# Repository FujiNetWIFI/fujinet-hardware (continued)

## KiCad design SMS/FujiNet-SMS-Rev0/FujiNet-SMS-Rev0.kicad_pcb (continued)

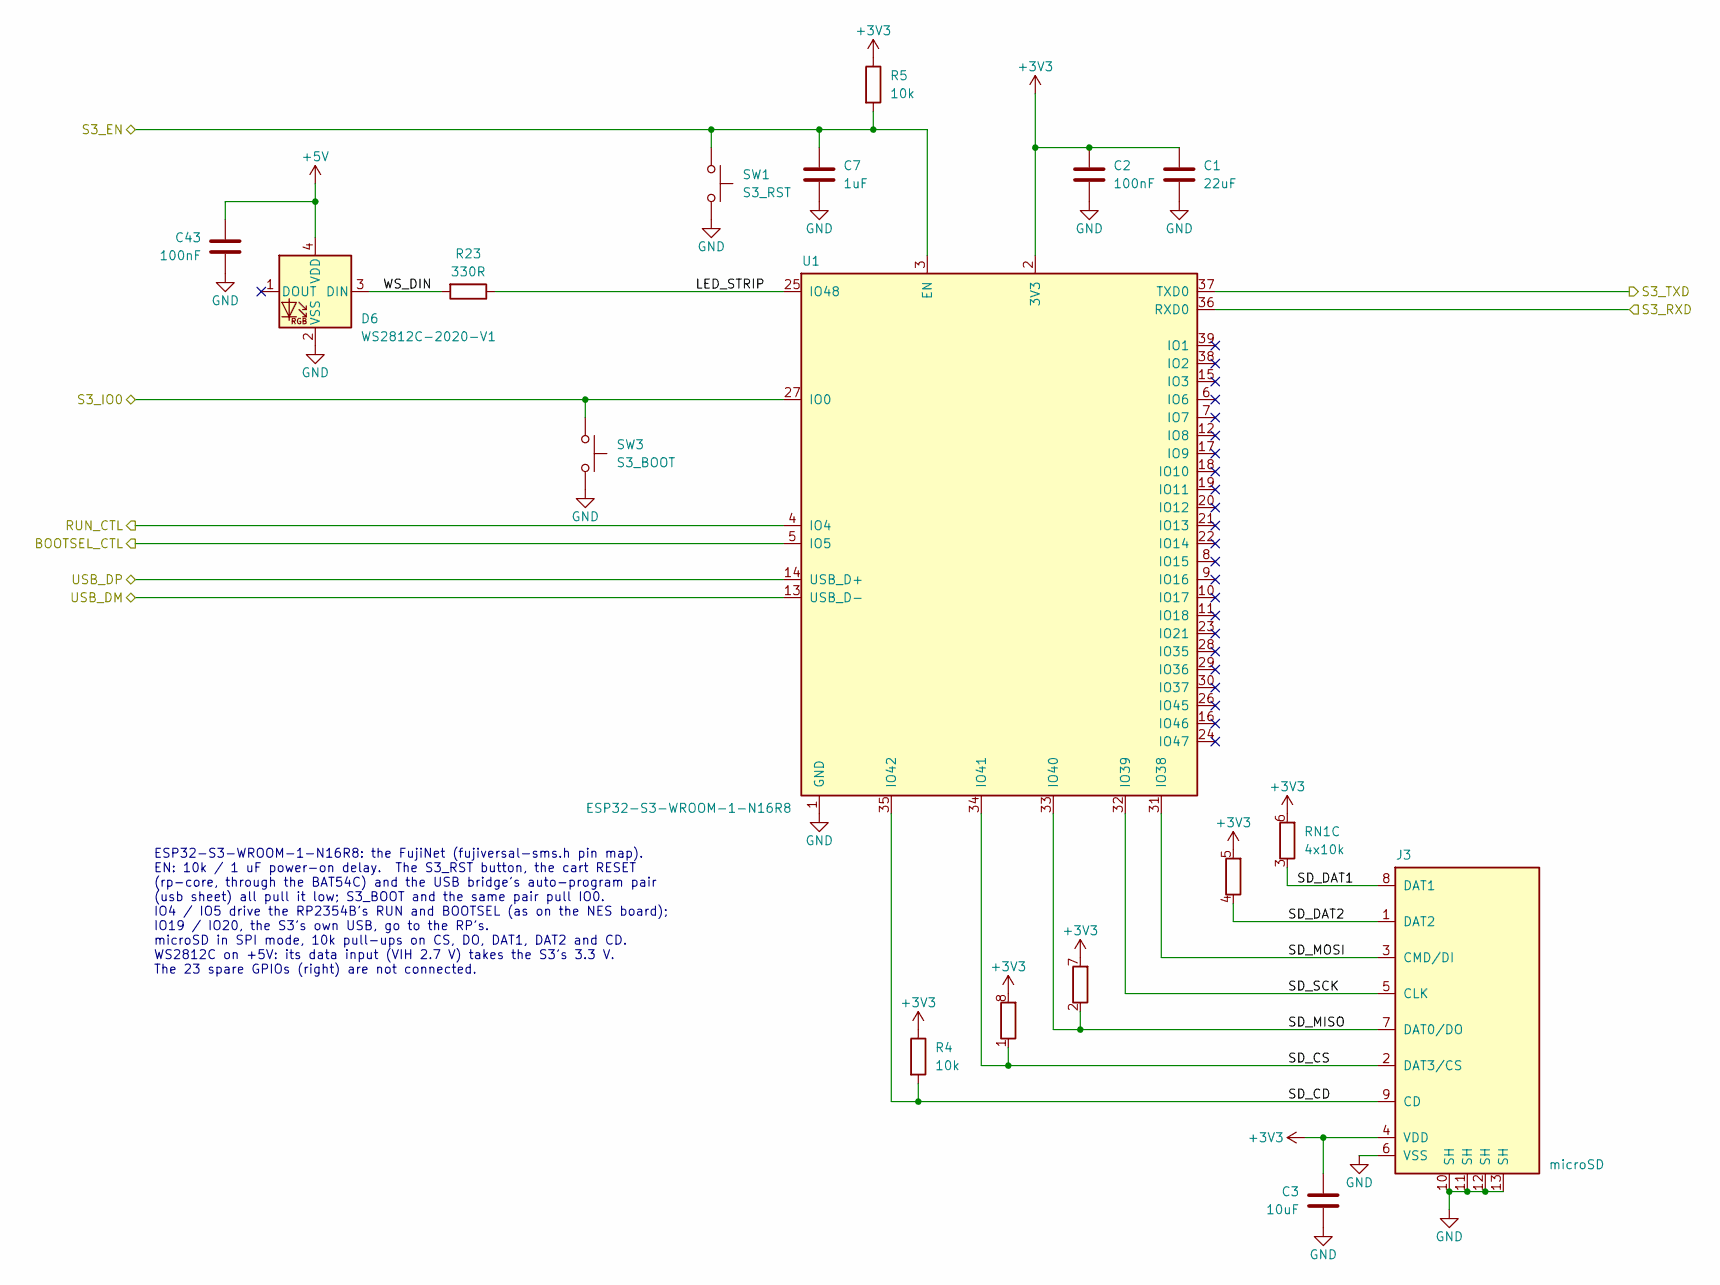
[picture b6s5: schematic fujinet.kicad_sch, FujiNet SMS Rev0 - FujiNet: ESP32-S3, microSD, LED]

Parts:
C1: 22uF; C_0805_2012Metric; MPN CL21A226MAQNNNE; LCSC C45783
C2, C43: 100nF; C_0603_1608Metric; MPN CC0603KRX7R9BB104; LCSC C14663
C3: 10uF; C_0603_1608Metric; MPN CL10A106KP8NNNC; LCSC C19702
C7: 1uF; C_0603_1608Metric; MPN CL10A105KB8NNNC; LCSC C15849
D6: WS2812C-2020-V1; LED_WS2812B-2020_PLCC4_2.0x2.0mm; MPN WS2812C-2020-V1; LCSC C2976072
J3: microSD; TF-SMD_TF-015; MPN TF-015; LCSC C113206
R4, R5: 10k; R_0603_1608Metric; MPN 0603WAF1002T5E; LCSC C25804
R23: 330R; R_0603_1608Metric; MPN 0603WAF3300T5E; LCSC C23138
RN1: 4x10k; R_Array_Convex_4x0603; MPN 4D03WGJ0103T5E; LCSC C29718
SW1: S3_RST; SW_SPST_TS-1187A; MPN TS-1187A-B-A-B; LCSC C318884
SW3: S3_BOOT; SW_SPST_TS-1187A; MPN TS-1187A-B-A-B; LCSC C318884
U1: ESP32-S3-WROOM-1-N16R8; ESP32-S3-WROOM-1; MPN ESP32-S3-WROOM-1-N16R8; LCSC C2913202

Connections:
+3V3: C1.1, C2.1, C3.1, J3.4 (VDD), R4.1, R5.1, RN1.5 (R4.2), RN1.6 (R3.2), RN1.7 (R2.2), RN1.8 (R1.2), U1.2 (3V3); also elsewhere on the board
+5V: C43.1, D6.4 (VDD); also elsewhere on the board
/BOOTSEL_CTL: U1.5 (IO5); also elsewhere on the board
/RUN_CTL: U1.4 (IO4); also elsewhere on the board
/S3_EN: C7.1, R5.2, SW1.1, U1.3 (EN); also elsewhere on the board
/S3_IO0: SW3.1, U1.27 (IO0); also elsewhere on the board
/S3_RXD: U1.36 (RXD0); also elsewhere on the board
/S3_TXD: U1.37 (TXD0); also elsewhere on the board
/USB_DM: U1.13 (USB_D-); also elsewhere on the board
/USB_DP: U1.14 (USB_D+); also elsewhere on the board
/fujinet/LED_STRIP: R23.1, U1.25 (IO48)
/fujinet/SD_CD: J3.9 (CD), R4.2, U1.35 (IO42)
/fujinet/SD_CS: J3.2 (DAT3/CS), RN1.1 (R1.1), U1.34 (IO41)
/fujinet/SD_DAT1: J3.8 (DAT1), RN1.3 (R3.1)
/fujinet/SD_DAT2: J3.1 (DAT2), RN1.4 (R4.1)
/fujinet/SD_MISO: J3.7 (DAT0/DO), RN1.2 (R2.1), U1.33 (IO40)
/fujinet/SD_MOSI: J3.3 (CMD/DI), U1.31 (IO38)
/fujinet/SD_SCK: J3.5 (CLK), U1.32 (IO39)
/fujinet/WS_DIN: D6.3 (DIN), R23.2
GND: C1.2, C2.2, C3.2, C7.2, C43.2, D6.2 (VSS), J3.6 (VSS), J3.10 (SH), J3.11 (SH), J3.12 (SH), J3.13 (SH), SW1.2, SW3.2, U1.1 (GND), U1.40 (GND), U1.41 (GND); also elsewhere on the board

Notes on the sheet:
ESP32-S3-WROOM-1-N16R8: the FujiNet (fujiversal-sms.h pin map). EN: 10k / 1 uF power-on delay. The S3_RST button, the cart RESET (rp-core, through the BAT54C) and the USB bridge's auto-program pair (usb sheet) all pull it low; S3_BOOT and the same pair pull IO0. IO4 / IO5 drive the RP2354B's RUN an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

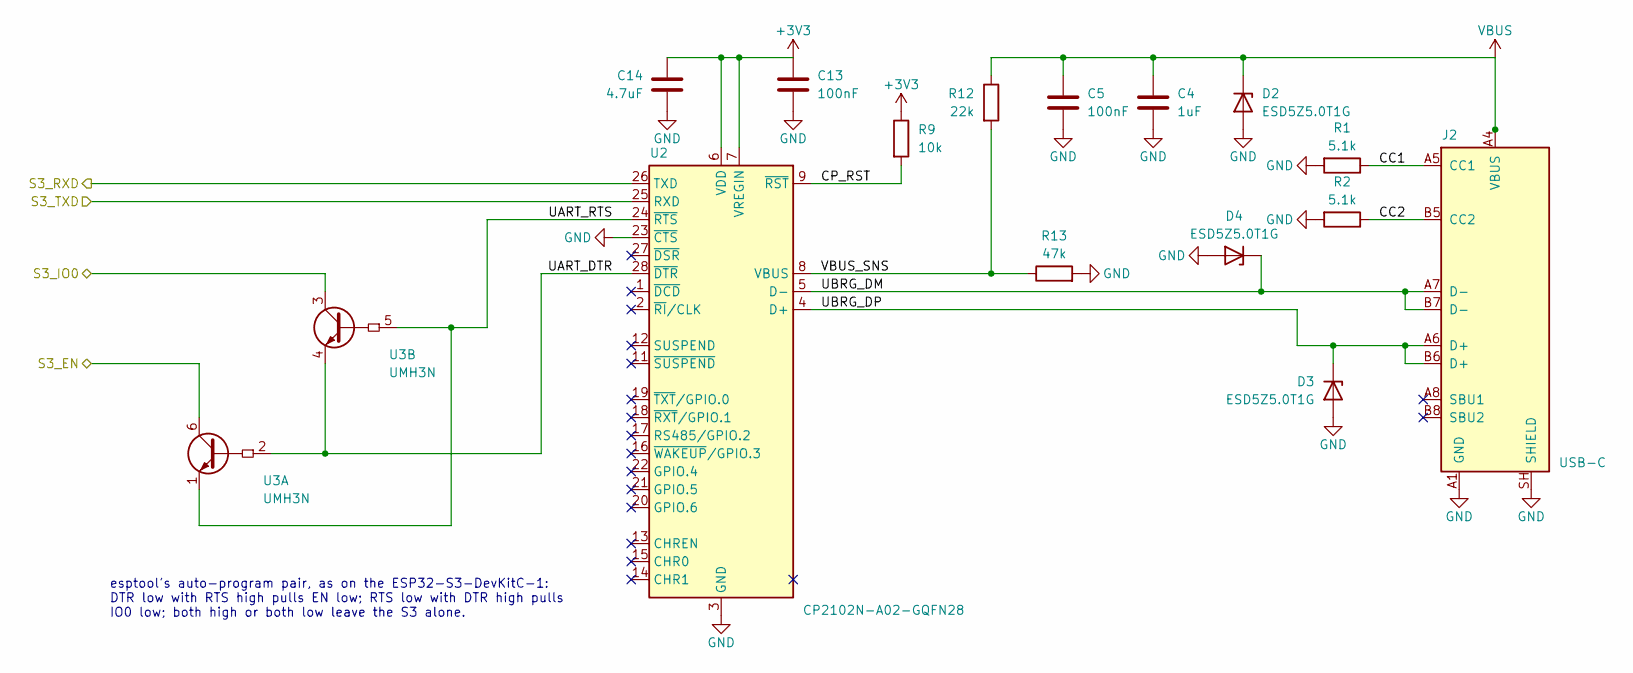
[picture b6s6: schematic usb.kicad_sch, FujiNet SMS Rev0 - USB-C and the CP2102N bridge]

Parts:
C4: 1uF; C_0603_1608Metric; MPN CL10A105KB8NNNC; LCSC C15849
C5, C13: 100nF; C_0603_1608Metric; MPN CC0603KRX7R9BB104; LCSC C14663
C14: 4.7uF; C_0603_1608Metric; MPN CL10A475KO8NNNC; LCSC C19666
D2, D3, D4: ESD5Z5.0T1G; D_SOD-523; MPN ESD5Z5.0T1G; LCSC C82044
J2: USB-C; USB_C_Receptacle_HRO_TYPE-C-31-M-12; MPN TYPE-C-31-M-12; LCSC C165948
R1, R2: 5.1k; R_0603_1608Metric; MPN 0603WAF5101T5E; LCSC C23186
R9: 10k; R_0603_1608Metric; MPN 0603WAF1002T5E; LCSC C25804
R12: 22k; R_0603_1608Metric; MPN 0603WAF2202T5E; LCSC C31850
R13: 47k; R_0603_1608Metric; MPN 0603WAF4702T5E; LCSC C25819
U2: CP2102N-A02-GQFN28; QFN-28-1EP_5x5mm_P0.5mm_EP3.35x3.35mm; MPN CP2102N-A02-GQFN28R; LCSC C964632
U3: UMH3N; SOT-363_SC-70-6; MPN UMH3N; LCSC C62892

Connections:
+3V3: C13.1, C14.1, R9.1, U2.6 (VDD), U2.7 (VREGIN); also elsewhere on the board
/S3_EN: U3.6 (C1); also elsewhere on the board
/S3_IO0: U3.3 (C2); also elsewhere on the board
/S3_RXD: U2.26 (TXD); also elsewhere on the board
/S3_TXD: U2.25 (RXD); also elsewhere on the board
/usb/CC1: J2.A5 (CC1), R1.1
/usb/CC2: J2.B5 (CC2), R2.1
/usb/CP_RST: R9.2, U2.9 (~RST)
/usb/UART_DTR: U2.28 (~DTR), U3.2 (B1), U3.4 (E2)
/usb/UART_RTS: U2.24 (~RTS), U3.1 (E1), U3.5 (B2)
/usb/UBRG_DM: D4.1 (K), J2.A7 (D-), J2.B7 (D-), U2.5 (D-)
/usb/UBRG_DP: D3.1 (K), J2.A6 (D+), J2.B6 (D+), U2.4 (D+)
/usb/VBUS_SNS: R12.2, R13.1, U2.8 (VBUS)
GND: C4.2, C5.2, C13.2, C14.2, D2.2 (A), D3.2 (A), D4.2 (A), J2.A1 (GND), J2.A12 (GND), J2.B1 (GND), J2.B12 (GND), J2.SH (SHIELD), R1.2, R2.2, R13.2, U2.3 (GND), U2.23 (~CTS), U2.29 (GND); also elsewhere on the board
VBUS: C4.1, C5.1, D2.1 (K), J2.A4 (VBUS), J2.A9 (VBUS), J2.B4 (VBUS), J2.B9 (VBUS), R12.1; also elsewhere on the board

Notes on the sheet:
esptool's auto-program pair, as on the ESP32-S3-DevKitC-1: DTR low with RTS high pulls EN low; RTS low with DTR high pulls IO0 low; both high or both low leave the S3 alone.

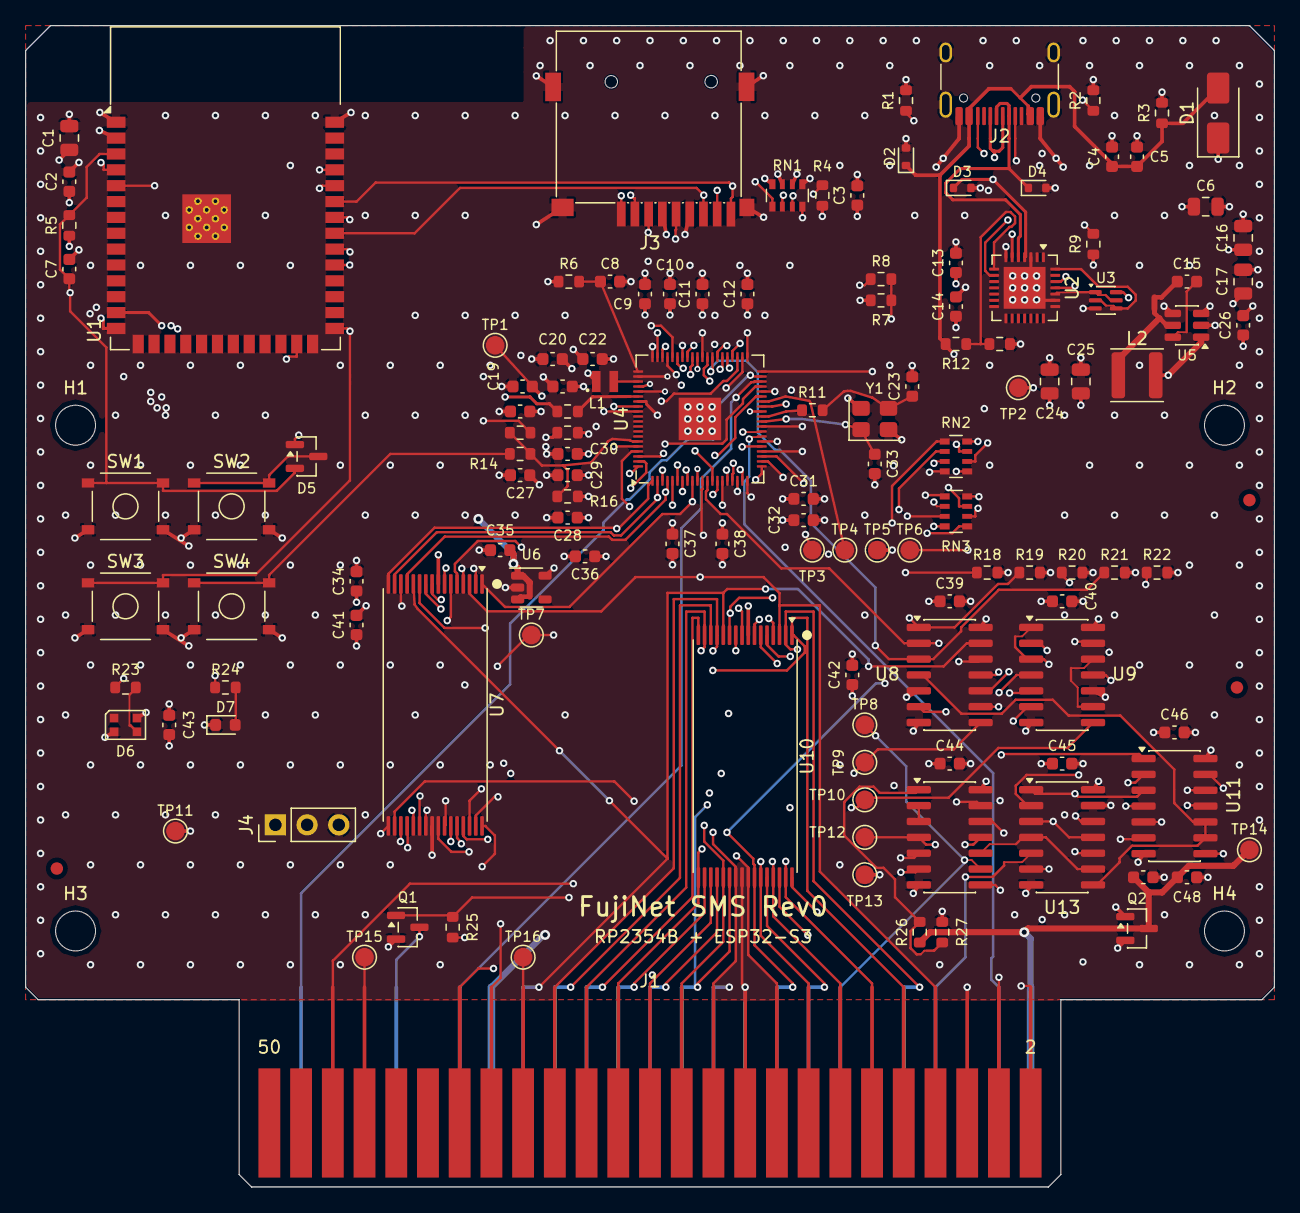
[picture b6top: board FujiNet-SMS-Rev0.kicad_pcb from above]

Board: 6 copper layers, 100.0 x 93.0 mm, 134 parts (0 on the bottom side), 126 nets.

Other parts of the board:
FID1, FID2, FID3: Fiducial_1mm_Mask2mm
H1, H2, H3, H4: MountingHole_3.2mm_NPTH

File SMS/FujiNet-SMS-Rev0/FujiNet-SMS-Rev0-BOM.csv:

"Refs","Value","Footprint","MPN","Manufacturer","LCSC","Description","DNP"
"C1,C6,C16,C17,C24,C25","22uF","C_0805_2012Metric","CL21A226MAQNNNE","Samsung Electro-Mechanics","C45783","S3 bulk (WiFi TX bursts)",""
"C4,C7,C35,C36","1uF","C_0603_1608Metric","CL10A105KB8NNNC","Samsung Electro-Mechanics","C15849","EN power-on delay",""
"C8,C14,C18,C21","4.7uF","C_0603_1608Metric","CL10A475KO8NNNC","Samsung Electro-Mechanics","C19666","VREG_VIN bulk (LDO rail)",""
"C23,C33","15pF","C_0603_1608Metric","CL10C150JB8NNNC","Samsung Electro-Mechanics","C1644","crystal load",""
"C3,C27,C41,C48","10uF","C_0603_1608Metric","CL10A106KP8NNNC","Samsung Electro-Mechanics","C19702","5V logic domain bulk",""
"C2,C5,C9,C10,C11,C12,C13,C15,C19,C20,C22,C26,C28,C29,C30,C31,C32,C34,C37,C38,C39,C40,C42,C43,C44,C45,C46,C47","100nF","C_0603_1608Metric","CC0603KRX7R9BB104","YAGEO","C14663","SRAM0 decoupling",""
"D1","SS34","D_SMA","SS34","MDD (Microdiode Semiconductor)","C8678","USB VBUS OR-ing (no back-feed into the console)",""
"D2,D3,D4","ESD5Z5.0T1G","D_SOD-523","ESD5Z5.0T1G","onsemi","C82044","ESD",""
"D5","BAT54C","SOT-23","BAT54C,215","Nexperia","C37704","RESET steering, common cathode",""
"D6","WS2812C-2020-V1","LED_WS2812B-2020_PLCC4_2.0x2.0mm","WS2812C-2020-V1","Worldsemi","C2976072","status LED on +5V (datasheet VDD 3.7-5.3 V; VIH 2.7 V takes the S3 3.3 V data directly)",""
"D7","red","LED_0603_1608Metric","KT-0603R","Hubei KENTO Elec","C2286","activity LED (GPIO33)",""
"J2","USB-C","USB_C_Receptacle_HRO_TYPE-C-31-M-12","TYPE-C-31-M-12","Korean Hroparts Elec","C165948","power + S3 programming",""
"J3","microSD","TF-SMD_TF-015","TF-015","SOFNG","C113206","microSD push-push, SPI mode",""
"J4","DBG UART","PinHeader_1x03_P2.54mm_Vertical","PZ254V-11-03P","XFCN","C2937625","RP debug UART: 1 TX (GPIO36), 2 RX (GPIO37), 3 GND; fit for bring-up","DNP"
"L1","3.3uH","RPI_L_AOTA-B201610S3R3","AOTA-B201610S3R3-101-T","Abracon","C42411119","RP2350 core SMPS inductor",""
"L2","6.8uH","L_Sunlord_SWPA4030S","SWPA4030S6R8MT","Sunlord","C62684","buck inductor",""
"Q1","2N7002","SOT-23","2N7002","Jiangsu Changjing (JSCJ)","C8545","console /WAIT pull-down (G = GPIO34)",""
"Q2","AO3401A","SOT-23","AO3401A","Alpha & Omega Semiconductor","C15127","console 5V switch: G = VBUS, S = +5V, D = CONS_5V; body diode CONS_5V -> +5V",""
"R1,R2","5.1k","R_0603_1608Metric","0603WAF5101T5E","UNI-ROYAL","C23186","UFP Rd",""
"R6","33R","R_0603_1608Metric","0603WAF330JT5E","UNI-ROYAL","C23140","VREG_AVDD filter",""
"R4,R5,R7,R9,R16","10k","R_0603_1608Metric","0603WAF1002T5E","UNI-ROYAL","C25804","RUN pull-up",""
"R13","47k","R_0603_1608Metric","0603WAF4702T5E","UNI-ROYAL","C25819","VBUS sense divider",""
"R10,R17","27R","R_0603_1608Metric","0603WAF270JT5E","UNI-ROYAL","C25190","USB series",""
"R23","330R","R_0603_1608Metric","0603WAF3300T5E","UNI-ROYAL","C23138","WS2812 data series",""
"R8,R11,R14,R15,R24","1k","R_0603_1608Metric","0603WAF1001T5E","UNI-ROYAL","C21190","activity LED series",""
"R3,R18,R19,R20,R21,R22,R25","4.7k","R_0603_1608Metric","0603WAF4701T5E","UNI-ROYAL","C23162","/WAIT held from power-on until the firmware drives GPIO34 low",""
"R12,R26","22k","R_0603_1608Metric","0603WAF2202T5E","UNI-ROYAL","C31850","console 5V sense divider",""
"R27","100k","R_0603_1608Metric","0603WAF1003T5E","UNI-ROYAL","C25803","console 5V sense -> 0.82 x CONS_5V",""
"RN1","4x10k","R_Array_Convex_4x0603","4D03WGJ0103T5E","UNI-ROYAL","C29718","SD pull-ups",""
"RN2,RN3","4x100R","R_Array_Convex_4x0603","4D03WGJ0101T5E","UNI-ROYAL","C25506","D0-D3 100R series (GPIO16-19)",""
"SW1","S3_RST","SW_SPST_TS-1187A","TS-1187A-B-A-B","XKB Connection","C318884","ESP32-S3 EN",""
"SW2","RESET","SW_SPST_TS-1187A","TS-1187A-B-A-B","XKB Connection","C318884","cart RESET: RP RUN + S3 EN via BAT54C",""
"SW3","S3_BOOT","SW_SPST_TS-1187A","TS-1187A-B-A-B","XKB Connection","C318884","ESP32-S3 BOOT (IO0)",""
"SW4","BOOTSEL","SW_SPST_TS-1187A","TS-1187A-B-A-B","XKB Connection","C318884","RP2354 BOOTSEL (hold while pressing RESET)",""
"U1","ESP32-S3-WROOM-1-N16R8","ESP32-S3-WROOM-1","ESP32-S3-WROOM-1-N16R8","Espressif","C2913202","FujiNet core (fujiversal-sms)",""
"U2","CP2102N-A02-GQFN28","QFN-28-1EP_5x5mm_P0.5mm_EP3.35x3.35mm","CP2102N-A02-GQFN28R","Silicon Labs","C964632","USB-UART for S3 flashing/console (self-powered)",""
"U3","UMH3N","SOT-363_SC-70-6","UMH3N","Jiangsu Changjing (JSCJ)","C62892","esptool auto-program (DevKitC-1 style)",""
"U4","RP2354B","QFN-80-1EP_10x10mm_P0.4mm_EP3.4x3.4mm","RP2354B","Raspberry Pi","C39843328","RP2350B + 2MB flash in package; cart bus server + bank lines",""
"U5","AP63203WU","TSOT-23-6","AP63203WU-7","Diodes Incorporated","C780769","3.3V 2A buck",""
"U6","AP2112K-3.3","SOT-23-5","AP2112K-3.3TRG1","Diodes Incorporated","C51118","RP2354B 3.3V LDO (IOVDD, VREG_VIN, VREG_AVDD), 600mA, fast start",""
"U8","74HCT10","SOIC-14_3.9x8.7mm_P1.27mm","74HCT10D,653","Nexperia","C547236","mailbox arena decode; RAM_WE window; SRAM /OE",""
"U9,U13","74HCT27","SOIC-14_3.9x8.7mm_P1.27mm","74HCT27D,653","Nexperia","C5984","the /WE strobe stage: WE_LOAD, WE_RAM, SRAM /WE",""
"U7,U10","AS6C4008-55TIN","TSOP-I-32_18.4x8mm_P0.5mm","AS6C4008-55TIN","Alliance Memory","C5569980","512Kx8 SRAM, 5 V: the lower 512K (SRAM A19 = 0)",""
"U11","74HCT00","SOIC-14_3.9x8.7mm_P1.27mm","SN74HCT00DR","Texas Instruments","C6764","CE & PWR_OK; LOAD window; /OE address term",""
"U12","74HCT14","SOIC-14_3.9x8.7mm_P1.27mm","SN74HCT14DR","Texas Instruments","C6769","PWR_OK from the console 5V sense; SRAM1 /CE = !A19; CE, A15, MBA inversions",""
"Y1","12MHz","Crystal_SMD_3225-4Pin_3.2x2.5mm","ABM8-272-T3","Abracon","C20625731","RP2350 12 MHz crystal",""

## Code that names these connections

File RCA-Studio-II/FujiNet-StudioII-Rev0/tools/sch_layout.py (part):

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def cart_bus(sh):
    """The cartridge bus, left to right from the slot: the edge on the left, every row of it level
    with the row it feeds; D7-D0 straight across through the 74HCT541 (drawn mirrored, its Y row
    facing the edge, its A row the RP2354B's GPIO23-16: the channels reversed, A8 / Y8 = bit 0, so the
    board's '541 meets the fingers and the RP with no crossing); /MRD on its own row, rising into the '541's
    /OE1, dropping into the CART CS NOR and running on through 330R to GPIO9; /DRIVE from GPIO24
    through an OR with PWR_OK_N into /OE2, /CLAIM from GPIO25 through the other OR into the NOR, each
    with its pull-up; PWR_OK_N one vertical line from the first OR to the second, the console-5 V
    sense's two Schmitt stages teed off it (the second into GPIO26); CART CS from the NOR back to
    the edge; MA0-MA7 and TPA straight across through their 330R to GPIO0-8.  The RP's right side:
    the debug header, the ADC divider, the LED, then the glue packages' supplies."""
    sh.wired = True
    # two crossings, both forced: /OE1 (/MRD, from the edge) sits between the '541's A pins and /OE2
    # (from the RP side), so the /MRD riser passes the /OE2 line; PWR_OK_N must reach both ORs, one
    # above the /MRD line (edge to GPIO9) and one below it, so it crosses that line once
    sh.crossing_budget = 2
    J, B, U, NOR = 'J_EDGE', 'U_BUF', 'U_RP', 'U_NOR'
    y0 = 50.8
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    # ---- /OE2 = /DRIVE | PWR_OK_N: the first OR (drawn mirrored), its output over the riser to /OE2 --
    ia, oa = gate(sh, 'U_OR', 1, (snap(xm + 10.16), oe2[1]), mirror='y', fields='below')
    sh.wire(oa, oe2)
    sh.label((snap(oa[0] - 1.27), oe2[1]), 'OE2_N', 'L')
    r24 = npin(sh, U, 'DRIVE_N', 1)
    assert r24[1] == ia['DRIVE_N'][0][1]
    x_pd, x_tpd = snap(xv + 30.48), snap(xv + 40.64)
    rail_line(sh, r24, [x_tpd, x_pd, ia['DRIVE_N'][0][0]])
    sh.label((snap(r24[0] - 1.27), r24[1]), 'DRIVE_N', 'L')
    fit(sh, 'R_PUDRIVE', 2, (x_pd, snap(r24[1] + 2.54)), {2: U_}, fields='right')
    sh.wire((x_pd, r24[1]), sh.P('R_PUDRIVE', 2))
    sh.sup(sh.P('R_PUDRIVE', 1), '+5V', rot=180)
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    # ---- CS_REQ_N = /CLAIM | PWR_OK_N: the second OR (mirrored), into the NOR's lower input ---------
    ib, ob = gate(sh, 'U_OR', 2, (snap(xv - 20.32), n2[1]), mirror='y', fields='below')
    sh.wire(ob, n2)
    sh.label((snap(n2[0] + 1.27), n2[1]), 'CS_REQ_N')
    r25 = npin(sh, U, 'CLAIM_N', 1)
    assert r25[1] == ib['CLAIM_N'][0][1]
    x_pc, x_tcl = snap(xv + 10.16), snap(xv + 22.86)
    rail_line(sh, r25, [x_tcl, x_pc, ib['CLAIM_N'][0][0]])
    sh.label((snap(r25[0] - 1.27), r25[1]), 'CLAIM_N', 'L')
    fit(sh, 'R_PUCLAIM', 2, (x_pc, snap(r25[1] - 2.54)), {2: D_}, fields='right')
    sh.wire((x_pc, r25[1]), sh.P('R_PUCLAIM', 2))
    sh.sup(sh.P('R_PUCLAIM', 1), '+5V')
    tee_tp(sh, 'TP_CLAIM', (x_tcl, r25[1]), up=False)
    # ---- PWR_OK: CONS_5V -> 22k / 100k -> '14 -> PWR_OK_N -> '14 -> GPIO26 ---------------------------
    yP = row(ROW['PWROK'])
    i1, o1 = gate(sh, 'U_INV', 1, (snap(xv - 2.54), snap(yP - 5.08)), fields='above')
    i2, o2 = gate(sh, 'U_INV', 2, (snap(xv + 17.78), yP), fields='above')
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    sh.wire(pa, (xv, pa[1]), (xv, o1[1]), (xv, yP), (xv, pb[1]), pb)
    sh.wire(o1, (xv, o1[1]))
    sh.wire((xv, yP), p2)
    sh.label((snap(pa[0] + 1.27), pa[1]), 'PWR_OK_N')
    vin = i1['VSENSE'][0]
    x_n = snap(vin[0] - 10.16)
    sh.wire((x_n, vin[1]), vin)
    sh.label((snap(x_n + 1.27), vin[1]), 'VSENSE')
    fit(sh, 'R_VSH', 2, (x_n, snap(vin[1] - 2.54)), {2: D_}, fields='right')
    sh.wire((x_n, vin[1]), sh.P('R_VSH', 2))
    sh.sup(sh.P('R_VSH', 1), 'CONS_5V')
    fit(sh, 'R_VSL', 1, (x_n, snap(vin[1] + 2.54)), {1: U_}, fields='right')
    sh.wire((x_n, vin[1]), sh.P('R_VSL', 1))
    sh.gnd(sh.P('R_VSL', 2))
    rpo = npin(sh, U, 'PWR_OK', 1)
    assert rpo[1] == yP
    x_tpp = snap(o2[0] + 7.62)
    rail_line(sh, o2, [x_tpp, rpo[0]])
    sh.label((snap(rpo[0] - 1.27), yP), 'PWR_OK', 'L')
    tee_tp(sh, 'TP_PWROK', (x_tpp, yP), up=False)
    # ---- /MRD: the edge -> the NOR, the '541's /OE1, 330R -> GPIO9 -----------------------------------
    yM = row(ROW['MRD'])
    em = E('MRD_N')
    assert em[1] == yM
    x_tp = snap(xE + 12.7)                             # the bring-up pads' column
    xd = snap(n1[0] + 5.08)                            # the drop into the NOR
    rgp9 = npin(sh, U, 'RP_MRD', 1)
    hres(sh, 'R_MRD', (snap(xRP - 20.32), yM))
    rail_line(sh, em, [x_tp, xd, xm, sh.P('R_MRD', 1)[0]])
    sh.label((snap(em[0] + 1.27), yM), 'MRD_N')
    tee_tp(sh, 'TP_MRD', (x_tp, yM), up=False)
    sh.wire((xd, yM), (xd, n1[1]), n1)
    sh.wire((xm, yM), (xm, oe1[1]), oe1)
    sh.label((snap(oe1[0] + 1.27), oe1[1]), 'MRD_N')
    sh.wire(sh.P('R_MRD', 2), rgp9)
    sh.label((snap(sh.P('R_MRD', 2)[0] + 1.27), yM), 'RP_MRD')
    # ---- CART CS: the NOR's output straight back to the edge ----------------------------------------
    ec = E('CART_CS')
    assert ec[1] == yN
    rail_line(sh, ec, [x_tp, x_no])
    sh.label((snap(ec[0] + 1.27), yN), 'CART_CS')
    tee_tp(sh, 'TP_CARTCS', (x_tp, yN), up=False)
    # ---- MA0-MA7, TPA: straight across through their 330R -----------------------------------------
    for i in range(9):
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    sh.gnd(sh.P(J, 7))
    # ---- the RP's right side: debug header, ADC divider, LED; spare GPIOs top and bottom -----------
    ncs(sh, U, 1)
    dtx, drx = npin(sh, U, 'DBG_TX', 1), npin(sh, U, 'DBG_RX', 1)
    fit(sh, 'J_DBG', 1, (snap(dtx[0] + 25.4), dtx[1]), {1: L_}, fields='right')
    sh.wire(dtx, sh.P('J_DBG', 1))
    sh.wire(drx, sh.P('J_DBG', 2))
    sh.label((snap(dtx[0] + 1.27), dtx[1]), 'DBG_TX')
    sh.label((snap(drx[0] + 1.27), drx[1]), 'DBG_RX')
    ground(sh, sh.P('J_DBG', 3))
    ad = npin(sh, U, 'VSENSE_ADC', 1)
    xa1, xa2, xa3 = snap(ad[0] + 15.24), snap(ad[0] + 25.4), snap(ad[0] + 35.56)
    rail_line(sh, ad, [xa1, xa2, xa3])
    sh.label((snap(ad[0] + 1.27), ad[1]), 'VSENSE_ADC')
    fit(sh, 'R_ADCH', 2, (xa1, snap(ad[1] - 2.54)), {2: D_}, fields='right')
    sh.wire((xa1, ad[1]), sh.P('R_ADCH', 2))
    sh.sup(sh.P('R_ADCH', 1), 'CONS_5V')
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    fit(sh, 'C_ADCF', 1, (xa3, snap(ad[1] + 2.54)), {1: U_}, fields='right')
    sh.wire((xa3, ad[1]), sh.P('C_ADCF', 1))
    sh.gnd(sh.P('C_ADCF', 2))
    led = npin(sh, U, 'RP_LED', 1)
    fit(sh, 'R_LED', 1, (snap(led[0] + 12.7), led[1]), {1: L_}, fields='above')
    sh.wire(led, sh.P('R_LED', 1))
    sh.label((snap(led[0] + 1.27), led[1]), 'RP_LED')
    fit(sh, 'D_LED', 2, (snap(sh.P('R_LED', 2)[0] + 12.7), led[1]), {2: L_}, fields='above')
    sh.wire(sh.P('R_LED', 2), sh.P('D_LED', 2))
    sh.label((snap(sh.P('R_LED', 2)[0] + 1.27), led[1]), 'RP_LED_A')
    ground(sh, sh.P('D_LED', 1))
    # ---- the glue packages' supplies and the 5V bulk, right of the RP; the spare gates at the foot ---
    xr0, ys0 = snap(led[0] + 7.62), row(ROW['MA'] + 6)
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            'the RP is unpowered or booting (they beat its reset pull-down; RP2350-E9).\n'
            "PWR_OK: edge 15 (the console's 5 V, before the mux) through %s / %s into\n"
            "two '14 Schmitt stages; the first, PWR_OK_N, gates the two ORs.  Every\n"
            'console line reaches the RP through 330R; GPIO0-31 are 5 V tolerant\n'
            'whenever IOVDD is up.  ADC0 (GPIO40) reads edge 15 through %s / %s.\n'
            'Edge pin 6 (ROM DISABLE) is grounded, as on a stock cartridge.'
            % (r('U_BUF'), r('U_OR'), r('U_NOR'), r('R_PUDRIVE'), r('R_PUCLAIM'), r('R_VSH'), r('R_VSL'),
               r('R_ADCH'), r('R_ADCL')), 1.27)
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        supply_pin(sh, P(n), R3, cap)
    for n, cap in ((51, 'C_DV51'), (32, 'C_DV32'), (10, 'C_DV10')):
        supply_pin(sh, P(n), DV, cap)
    supply_pin(sh, P(65), DV)                          # VREG_FB senses DVDD
    for n in (62, 81):
        supply_pin(sh, P(n), 'GND')
    i76 = P(76)                                        # the IO rail's bulk, on IOVDD 76's run
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    lx = P(63)
    fit(sh, 'L_RP', 2, (lx[0], snap(lx[1] - 10.16)), {2: D_}, fields='right')
    sh.wire(lx, sh.P('L_RP', 2))
    sh.label((lx[0], snap(lx[1] - 1.27)), 'RP_LX', 'U')
    sh.sup(sh.P('L_RP', 1), DV)
    av = P(61)
    tee = (av[0], snap(av[1] - 12.7))
    fit(sh, 'R_AVDD', 2, tee, {2: D_}, fields='right')
    sh.wire(av, tee)
    sh.label((av[0], snap(av[1] - 1.27)), 'VREG_AVDD', 'U')
    sh.sup(sh.P('R_AVDD', 1), R3)
    st = (snap(tee[0] + 12.7), tee[1])
    sh.wire(tee, st)
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        sh.hlabel(Pt(xr, y, 1, 0), net, 'R', 'bidirectional')
    # QSPI_SS: up to the BOOTSEL row, the pull-up on a tee to the left
    ss = P(75)
    sh.label((ss[0], snap(ss[1] - 1.27)), 'QSPI_SS', 'U')
    sh.wire(ss, (ss[0], snap(y_ss + 5.08)), (ss[0], y_ss), (ss[0], y_bs))
    xs = snap(ss[0] - 5.08)
    sh.wire((ss[0], y_ss), (xs, y_ss))
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    fit(sh, 'R_BSELCTL', 2, (snap(xc + 2.54), y_ct), {2: L_}, fields='below')
    sh.wire((xc, y_ct), sh.P('R_BSELCTL', 2))
    sh.wire(sh.P('R_BSELCTL', 1), (xr, y_ct))
    sh.hlabel(Pt(xr, y_ct, 1, 0), 'BOOTSEL_CTL', 'R', 'input')
    fit(sh, 'R_BSEL', 1, (snap(ss[0] + 7.62), y_bs), {1: L_}, fields='above')
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
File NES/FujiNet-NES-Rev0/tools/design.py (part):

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KiCad files are generated output.

Circuit provenance: FujiNet-Astrocade-Rev0 (this repository), itself from the
INTV Rev0 cart / PiNTY CARD (CERN-OHL-W-2.0).  Firmware contracts:
  fujinet-firmware pico/nes/firmware/include/nes_cart.h   (RP pins, '595 bits)
  fujinet-firmware pico/nes/README.md                     (decode equations)
  fujinet-firmware include/pinmap/fujiversal-nes.h        (S3 pins)
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NC = None  # explicit no-connect

SHEETS = [  # (file stem, title, page) -- in signal-flow order, console side first
    ('edge-cic', '72-pin cart edge, CIClone', 2),
    ('rp2354b', 'RP2354B bus controller', 3),
    ('sram', 'PRG and CHR SRAM', 4),
    ('glue', "5V glue logic, '595 control bits", 5),
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# nes_cart.h: all 48 GPIOs.
RP_GPIO_NET = {g: 'CA%d' % g for g in range(13)}                    # CA0_PIN 0
RP_GPIO_NET.update({13 + i: 'CD%d' % i for i in range(8)})          # CD0_PIN 13
RP_GPIO_NET.update({21: 'M2', 22: 'RW', 23: 'ROMSEL_N', 24: 'CA13', 25: 'CA14',
                    26: 'PA10', 27: 'PA11', 28: 'PA12',
                    29: 'SR_SER', 30: 'SR_SCK', 31: 'SR_RCK', 32: 'IRQ_N'})
RP_GPIO_NET.update({33 + i: 'PRG_A%d' % (13 + i) for i in range(6)})   # PRG_BANK_PIN 33
RP_GPIO_NET.update({39 + i: 'CHR_A%d' % (10 + i) for i in range(9)})   # CHR_BANK_PIN 39
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        13: ('CA0', 'CPU A0'), 14: ('RW', 'CPU R/W'), 15: ('IRQ_N', '~{IRQ}'),
        16: (NC, 'EXP0'), 17: (NC, 'EXP1'), 18: (NC, 'EXP2'), 19: (NC, 'EXP3'), 20: (NC, 'EXP4'),
        21: ('PPU_RD_N', 'PPU ~{RD}'), 22: ('CIRAM_A10', 'CIRAM A10'),
        23: ('PA6', 'PPU A6'), 24: ('PA5', 'PPU A5'), 25: ('PA4', 'PPU A4'), 26: ('PA3', 'PPU A3'),
        27: ('PA2', 'PPU A2'), 28: ('PA1', 'PPU A1'), 29: ('PA0', 'PPU A0'),
        30: ('PD0', 'PPU D0'), 31: ('PD1', 'PPU D1'), 32: ('PD2', 'PPU D2'), 33: ('PD3', 'PPU D3'),
        34: ('CIC_TOPAK', 'CIC toPak'), 35: ('CIC_TOMB', 'CIC toMB'), 36: ('CONS_5V', '+5V'),
        37: (NC, 'SYSTEM CLK'), 38: ('M2', 'M2'), 39: ('CA12', 'CPU A12'), 40: ('CA13', 'CPU A13'),
        41: ('CA14', 'CPU A14'), 42: ('CD7', 'CPU D7'), 43: ('CD6', 'CPU D6'), 44: ('CD5', 'CPU D5'),
        45: ('CD4', 'CPU D4'), 46: ('CD3', 'CPU D3'), 47: ('CD2', 'CPU D2'), 48: ('CD1', 'CPU D1'),
        49: ('CD0', 'CPU D0'), 50: ('ROMSEL_N', '~{ROMSEL}'),
        51: (NC, 'EXP9'), 52: (NC, 'EXP8'), 53: (NC, 'EXP7'), 54: (NC, 'EXP6'), 55: (NC, 'EXP5'),
        56: ('PPU_WR_N', 'PPU ~{WR}'), 57: ('CIRAM_CE_N', 'CIRAM ~{CE}'), 58: ('PA13_N', 'PPU ~{A13}'),
        59: ('PA7', 'PPU A7'), 60: ('PA8', 'PPU A8'), 61: ('PA9', 'PPU A9'), 62: ('PA11', 'PPU A11'),
        63: ('PA10', 'PPU A10'), 64: ('PA12', 'PPU A12'), 65: ('PA13', 'PPU A13'),
        66: ('PD7', 'PPU D7'), 67: ('PD6', 'PPU D6'), 68: ('PD5', 'PPU D5'), 69: ('PD4', 'PPU D4'),
        70: ('CIC_RST', 'CIC +RST'), 71: ('CIC_CLK', 'CIC CLK'), 72: ('GND', 'GND')}

# AS6C4008 32-pin TSOP-I / sTSOP pin assignment (Alliance datasheet, PIN
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      70: NC, 71: NC, 72: NC, 73: NC, 74: NC,                                 # QSPI (flash in package)
      75: 'QSPI_SS', 81: 'GND'}
rp.update({p: RP_IO_RAIL for p in RP_IOVDD_PINS})
rp.update({p: 'DVDD' for p in RP_DVDD_PINS})
for g, pin in RP_GPIO_PIN.items():
    rp[pin] = RP_GPIO_NET[g]
add('U', 'MCU_RaspberryPi:RP2354B', 'RP2354B', FP('QFN-80-1EP_10x10mm_P0.4mm_EP3.4x3.4mm'), rp,
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add('J', '%s:NES_Cart_Edge_72' % LIB, 'NES_Cart_Edge_72', FP('NES_Cart_Edge_72'),
    {k: v[0] for k, v in EDGE.items()}, desc='72-pin NES cartridge edge, 2.50 mm pitch', bom=False)
sheet('rp2354b')
# decoupling: one 100nF per IOVDD/DVDD/QSPI/USB/ADC supply pin, bulk on each rail
for _ in RP_IOVDD_PINS:
    C('100nF', RP_IO_RAIL, desc='IOVDD decoupling')
C('100nF', RP_IO_RAIL, desc='QSPI_IOVDD decoupling')
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     ['CD%d' % i for i in range(8)], 'PRG_CE_N', 'PRG_OE_N', 'PRG_WE_N',
     desc='PRG SRAM 512Kx8: $8000-$FFFF through the 4 x 8K bank table (GP33-38)')
SRAM(['PA%d' % i for i in range(10)] + ['CHR_A%d' % i for i in range(10, 19)],
     ['PD%d' % i for i in range(8)], 'PA13', 'CHR_OE_N', 'CHR_WE_N',
     desc='CHR SRAM 512Kx8: PPU $0000-$1FFF through the 8 x 1K bank table (GP39-47)')
C('100nF', '+5V', desc='PRG SRAM decoupling')
C('100nF', '+5V', desc='CHR SRAM decoupling')
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   desc="'595 enables default low while /OE is high")
RN('4x100k', ['MIR0', 'MIR1', 'SR_LED', 'SR_SPARE'], 'GND',
   desc="'595 remaining bits defined while /OE is high")
# -- 74HCT253: a = CIRAM A10 = {PA10, PA11, 0, 1}[MIR1:MIR0]; b = CIRAM /CE pass-through
# (all four inputs the same, so the select is irrelevant).  Both halves
# tri-state on PWR_OK_N: nothing drives the console's CIRAM pins while it is off.
add('U', '%s:74HCT253' % LIB, '74HCT253', SOIC16,
    {1: 'PWR_OK_N', 6: 'PA10', 5: 'PA11', 4: 'GND', 3: '+5V', 7: 'CIRAM_A10',   # /OEa I0a I1a I2a I3a Za
     14: 'MIR0', 2: 'MIR1',                                                    # A0 A1 (shared selects)
     15: 'PWR_OK_N', 10: 'CIRAM_CE_PRE', 11: 'CIRAM_CE_PRE', 12: 'CIRAM_CE_PRE', 13: 'CIRAM_CE_PRE',
     9: 'CIRAM_CE_N',                                                          # /OEb I0b..I3b Zb
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       [('PPU_RD_N', 'PWR_OK_N', 'CHR_OE_N'),         # /OE = !(!/RD & PWR_OK)
        ('PPU_WR_N', 'CHR_WE_EN_N', 'CHR_WE_N'),      # /WE = /WR | !CHR_WE_EN
        ('GND', 'GND', NC),
        ('PA13_N', 'FOURSCREEN', 'CIRAM_CE_PRE')],    # CIRAM /CE = /A13 | FOURSCREEN, then the '253b gate
       desc='CHR SRAM /OE, /WE; CIRAM /CE (pre-gate)')
for n in ('74HCT595', '74HCT253', '74HCT14', '74HCT20', '74HCT00', '74HCT32'):
    C('100nF', '+5V', desc=n + ' VCC decoupling')
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sheet('edge-cic')
# -- CIClone: 10NES lockout clone on the four CIC fingers, DNP until its
# firmware is in hand.  Pin map = the common ATtiny13A NES CIC clone
# (avrciczz / "ciclone"): PB3 CLK, PB0 DOUT (toMB), PB1 DIN (toPak), PB2 RST;
# PB4 (LED) and /RESET open.  Powered from the console (CONS_5V) so it resets
# with it.  Programmable through the fingers + the /RESET pad.
add('U', 'MCU_Microchip_ATtiny:ATtiny13A-SS', 'ATtiny13A-SSU', FP('SOIC-8_3.9x4.9mm_P1.27mm'),
    {1: 'CIC_RESET_N', 2: 'CIC_CLK', 3: NC, 4: 'GND', 5: 'CIC_TOMB', 6: 'CIC_TOPAK', 7: 'CIC_RST', 8: 'CONS_5V'},
    mpn='ATTINY13A-SSUR', lcsc='C40382', desc='CIClone (10NES key), DNP: PB3=CLK PB0=toMB PB1=toPak PB2=+RST', dnp=True)
C('100nF', 'CONS_5V', desc='CIClone decoupling', dnp=True)
TP('CIC_RESET_N', 'CIC_RST')

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
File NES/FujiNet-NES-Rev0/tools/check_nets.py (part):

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# nesdev wiki, "Cartridge connector", 72-pin NES.  Pin N and N+36 share a position.
EDGE = {1: 'GND', 2: 'A11', 3: 'A10', 4: 'A9', 5: 'A8', 6: 'A7', 7: 'A6', 8: 'A5', 9: 'A4',
        10: 'A3', 11: 'A2', 12: 'A1', 13: 'A0', 14: 'R/W', 15: '/IRQ', 16: 'EXP0', 17: 'EXP1',
        18: 'EXP2', 19: 'EXP3', 20: 'EXP4', 21: 'PPU /RD', 22: 'CIRAM A10', 23: 'PA6', 24: 'PA5',
        25: 'PA4', 26: 'PA3', 27: 'PA2', 28: 'PA1', 29: 'PA0', 30: 'PD0', 31: 'PD1', 32: 'PD2',
        33: 'PD3', 34: 'CIC toPak', 35: 'CIC toMB', 36: '+5V', 37: 'SYSTEM CLK', 38: 'M2',
        39: 'A12', 40: 'A13', 41: 'A14', 42: 'D7', 43: 'D6', 44: 'D5', 45: 'D4', 46: 'D3',
        47: 'D2', 48: 'D1', 49: 'D0', 50: '/ROMSEL', 51: 'EXP9', 52: 'EXP8', 53: 'EXP7',
        54: 'EXP6', 55: 'EXP5', 56: 'PPU /WR', 57: 'CIRAM /CE', 58: 'PPU /A13', 59: 'PA7',
        60: 'PA8', 61: 'PA9', 62: 'PA11', 63: 'PA10', 64: 'PA12', 65: 'PA13', 66: 'PD7',
        67: 'PD6', 68: 'PD5', 69: 'PD4', 70: 'CIC +RST', 71: 'CIC CLK', 72: 'GND'}
UNUSED = ('EXP', 'SYSTEM CLK')
CIC = {'CIC toPak': 'PB1', 'CIC toMB': 'PB0', 'CIC +RST': 'PB2', 'CIC CLK': 'PB3'}   # avrciczz pin map
GATES4 = [(1, 2, 3), (4, 5, 6), (9, 10, 8), (12, 13, 11)]          # 74xx00/08/32
INV6 = [(1, 2), (3, 4), (5, 6), (9, 8), (11, 10), (13, 12)]          # 74xx14

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
    # ---- firmware pin contracts ----
    cart = 'pico/nes/firmware/include/nes_cart.h'
    P = {k: define(cart, k + '_PIN') for k in ('CA0', 'CD0', 'M2', 'RW', 'ROMSEL', 'CA13', 'PA10',
                                               'SR_SER', 'SR_SCK', 'SR_RCK', 'IRQ', 'PRG_BANK', 'CHR_BANK')}
    SR = {k: define(cart, 'SR_' + k).bit_length() - 1 for k in
          ('SRAM_EN', 'PRG_WE_EN', 'CHR_WE_EN', 'MIR0', 'MIR1', 'FOURSCREEN', 'LED', 'SPARE')}
    Q = lambda bit: func_net.get((U595, 'Q' + 'ABCDEFGH'[SR[bit]]))
    pm = 'include/pinmap/fujiversal-nes.h'
    sd = {k: define(pm, 'PIN_SD_HOST_' + k) for k in ('CS', 'SCK', 'MISO', 'MOSI')}
    led_strip = define(pm, 'PIN_LED_STRIP')
    uart_rx, uart_tx = define(pm, 'PIN_UART0_RX'), define(pm, 'PIN_UART0_TX')
    run_io, bsel_io = define(pm, 'PIN_RP2040_RUN', -1), define(pm, 'PIN_RP2040_BOOTSEL', -1)
    if run_io < 0 or bsel_io < 0:
        alt = 'include/pinmap/fujiversal-intv.h'
        run_io, bsel_io = define(alt, 'PIN_RP2040_RUN'), define(alt, 'PIN_RP2040_BOOTSEL')
        print('note: %s does not define PIN_RP2040_RUN/BOOTSEL yet; using %s (IO%d/IO%d)' % (pm, alt, run_io, bsel_io))
    chk('nes_cart.h uses all 48 GPIOs (CHR_BANK_PIN + 9 == 48)', P['CHR_BANK'] + 9 == 48)
    chk("'595 bits are the eight distinct positions 0..7", sorted(SR.values()) == list(range(8)))

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            d = int(s[1:])
            chk('J1.%d CPU %s -> GP%d' % (p, s, P['CD0'] + d), n == rp(P['CD0'] + d))
    for k in range(3):
        chk('J1 PPU A%d -> GP%d' % (10 + k, P['PA10'] + k), sig['PA%d' % (10 + k)] == rp(P['PA10'] + k))
    irq = sig['/IRQ']
    chk('/IRQ net has only J1 and U1 (the console holds the pull-up)',
        all(r in (J1, U1) for (r, _, _) in nets.get(irq, [])))
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        chk('CHR A%d = GP%d' % (10 + i, P['CHR_BANK'] + i), func_net.get((CHR, 'A%d' % (10 + i))) == rp(P['CHR_BANK'] + i))
    for i in range(8):
        chk('CHR DQ%d = PPU D%d' % (i, i), func_net.get((CHR, 'DQ%d' % i)) == sig['PD%d' % i])
    chk('CHR /CE = PPU A13', func_net.get((CHR, '~{CE}')) == sig['PA13'])
    for r in (PRG, CHR):
        chk('%s VCC on the 5V logic rail, VSS on GND' % r,
            func_net.get((r, 'VCC')) == v5 and func_net.get((r, 'VSS')) == 'GND')
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    chk('CIRAM /CE pre-gate = PPU /A13 | FOURSCREEN', ce_pre is not None)
    m = lambda f: func_net.get((U253, f))
    chk("'253 I0a = PPU A10, I1a = PPU A11, I2a = 0, I3a = 1",
        m('I0a') == sig['PA10'] and m('I1a') == sig['PA11'] and m('I2a') == 'GND' and m('I3a') == v5)
    chk("'253 selects A0 = MIR0, A1 = MIR1", m('A0') == Q('MIR0') and m('A1') == Q('MIR1'))
    chk("'253 Za = CIRAM A10, /OEa = PWR_OK_N", m('Za') == sig['CIRAM A10'] and m('OEa') == pwr_ok_n)
    chk("'253 half b: I0b..I3b = CIRAM /CE pre-gate, Zb = CIRAM /CE, /OEb = PWR_OK_N",
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    chk('RP USB_DP -> 27R -> S3 USB_D+ (IO20)', through_r(func_net.get((U1, 'USB_DP')), func_net.get((U2, 'USB_D+'))) == '27R')
    chk('RP USB_DM -> 27R -> S3 USB_D- (IO19)', through_r(func_net.get((U1, 'USB_DM')), func_net.get((U2, 'USB_D-'))) == '27R')
    run, ss = func_net.get((U1, 'RUN')), func_net.get((U1, '~{QSPI_SS}'))
    chk('S3 IO%d (PIN_RP2040_RUN) -> 1k -> RP RUN (active low, no inverter)' % run_io, through_r(s3(run_io), run) == '1k')
    chk('S3 IO%d (PIN_RP2040_BOOTSEL) -> 1k -> RP QSPI_SS' % bsel_io, through_r(s3(bsel_io), ss) == '1k')
    chk('RUN pull-up to the IO rail', through_r(run, v33io) == '10k')
    chk('QSPI_SS pull-up to the IO rail', through_r(ss, v33io) == '10k')
    for f in ('QSPI_SCLK', 'QSPI_SD0', 'QSPI_SD1', 'QSPI_SD2', 'QSPI_SD3'):
        chk('RP %s unconnected (flash is in the package)' % f, unconn(func_net.get((U1, f))))
    for n, nodes in nets.items():   # every supply pin (names repeat: IOVDD x8, DVDD x3)
        for (ref, pin, f) in nodes:
            if ref == U1 and f in ('IOVDD', 'QSPI_IOVDD', 'USB_OTP_VDD', 'ADC_AVDD'):
                chk('RP %s (pin %s) on %s' % (f, pin, v33io), n == v33io)
            if ref == U1 and f == 'VREG_VIN':
                chk('RP %s (pin %s) on %s' % (f, pin, v33io), n == v33io)
            if ref == U1 and f == 'DVDD':
                chk('RP DVDD (pin %s) on DVDD' % pin, n == func_net.get((U1, 'VREG_FB')))
            if ref == U1 and f in ('GND', 'VREG_PGND'):
                chk('RP %s (pin %s) on GND' % (f, pin), n == 'GND')
    for f in ('SWCLK', 'SWDIO', 'RUN'):
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    chk('J2 VDD on %s, VSS on GND' % v33, node_net.get((J2, '4')) == v33 and node_net.get((J2, '6')) == 'GND')
    ws_din = node_net.get((WS, '3'))
    chk('LED strip IO%d -> R -> WS2812 DIN' % led_strip, through_r(s3(led_strip), ws_din) is not None)
    chk('PIN_UART0_TX/RX are the module TXD0/RXD0 pads (GPIO43/44)', (uart_tx, uart_rx) == (43, 44))
    chk('S3 TXD0 -> CP2102N RXD', func_net.get((U2, 'TXD0')) == func_net.get((UCP, 'RXD')))
    chk('S3 RXD0 <- CP2102N TXD', func_net.get((U2, 'RXD0')) == func_net.get((UCP, 'TXD')))
    for io in (3, 45, 46):
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    # ---- CIClone (DNP): console-powered, resets with it; /RESET on a pad ----
    chk('CIClone VCC on edge +5V (CONS_5V), GND on GND',
        func_net.get((CIC_U, 'VCC')) == cons and func_net.get((CIC_U, 'GND')) == 'GND')
    chk('CIClone /RESET on a test pad', any(r.startswith('TP') for (r, _, _) in nets.get(func_net.get((CIC_U, '~{RESET}/PB5')), [])))

    # ---- edge footprint orientation, from the footprint file itself ----
    fpt = open(os.path.join(PRJ, 'FujiNet-NES.pretty', 'NES_Cart_Edge_72.kicad_mod')).read()
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
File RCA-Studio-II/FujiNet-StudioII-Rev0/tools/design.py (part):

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One cart, two MCUs, as on FujiNet-ChannelF Rev0: the RP2354B serves the console's bus, and the
ESP32-S3-WROOM-1 (the FujiNet, fujiversal-studio2) is its USB host over an on-board USB link, with a
microSD, a WS2812 status light and a CP2102N USB-C bridge for flashing it.  The S3 also holds the
RP2354B's RUN and BOOTSEL (IO4 / IO5, the fujiversal-intv pins), so it can re-flash it.

Circuit provenance: FujiNet-5200 Rev0 (this repository's ATARI-5200) for the RP2354B core, the
'541 data buffer, the PWR_OK and ADC senses, the debug header and the generators; FujiNet-ChannelF
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NC = None  # explicit no-connect

SHEETS = [  # (file stem, title, page)
    ('cart-bus', "Cart bus: edge, glue, RP GPIO", 2),
    ('rp-core', 'RP2354B core, crystal, RUN, SWD', 3),
    ('fujinet', 'FujiNet (ESP32-S3), microSD', 4),
    ('usb', 'USB-C + CP2102N', 5),
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          'IO40': 'SD_MISO', 'IO41': 'SD_CS', 'IO42': 'SD_CD', 'IO48': 'LED_STRIP',
          'RXD0': 'S3_RXD', 'TXD0': 'S3_TXD'}

# s2_cart.h.  GPIO0-31 are the 5 V-tolerant bus pins; GPIO40-47 are not and carry only the ADC
# sense and the 3.3 V debug header.  The console's lines reach the RP through 330R (RP_*).
RP_GPIO_NET = {i: 'RP_MA%d' % i for i in range(8)}                  # MA0_PIN 0: MA0-MA7
RP_GPIO_NET.update({8: 'RP_TPA', 9: 'RP_MRD'})                      # TPA_PIN, MRD_PIN
RP_GPIO_NET.update({g: NC for g in range(10, 16)})
RP_GPIO_NET.update({16 + i: 'RP_D%d' % i for i in range(8)})        # D0_PIN 16: into the '541
RP_GPIO_NET.update({24: 'DRIVE_N', 25: 'CLAIM_N', 26: 'PWR_OK', 27: 'RP_LED'})
RP_GPIO_NET.update({g: NC for g in range(28, 40)})
RP_GPIO_NET.update({40: 'VSENSE_ADC', 41: NC, 42: NC, 43: NC, 44: 'DBG_TX', 45: 'DBG_RX', 46: NC, 47: NC})
assert len(RP_GPIO_NET) == 48 and set(RP_GPIO_NET) == set(RP_GPIO_PIN)

# RCA Studio II 22-pin cartridge edge, 0.156" pitch, contacts on one face: (net, symbol pin name).
# The console's CN1 is a 2x22 connector whose lettered row is unconnected (EJK's schematic); a cart
# carries its 22 contacts on one face (FliP's multicart, the original board: tools/edge_geom.py).  Pin 6 is the console's ROM DISABLE: grounded, as a cart does, it removes the
# built-in games at $0400-$07FF.  Pin 19 is TPA gated by /MRD in the console: it pulses on memory
# reads only.  Pin 22 is the cart's CART CS output: high turns the console RAM off.
EDGE = {1: ('D7', 'D7'), 2: ('D6', 'D6'), 3: ('D5', 'D5'), 4: ('D4', 'D4'), 5: ('D3', 'D3'),
        6: ('GND', '~{ROM_DIS}'), 7: ('GND', 'GND'), 8: ('D2', 'D2'), 9: ('D1', 'D1'), 10: ('D0', 'D0'),
        11: ('MA0', 'MA0'), 12: ('MA1', 'MA1'), 13: ('MA2', 'MA2'), 14: ('MA3', 'MA3'),
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      70: NC, 71: NC, 72: NC, 73: NC, 74: NC,                                 # QSPI (flash in package)
      75: 'QSPI_SS', 81: 'GND'}
rp.update({p: RP_IO_RAIL for p in RP_IOVDD_PINS})
rp.update({p: 'DVDD' for p in RP_DVDD_PINS})
for g, pin in RP_GPIO_PIN.items():
    rp[pin] = RP_GPIO_NET[g]
U_RP = add('U', '%s:RP2354B_Split' % LIB, 'RP2354B', FP('QFN-80-1EP_10x10mm_P0.4mm_EP3.4x3.4mm'), rp,
           mpn='RP2354B', lcsc='C39843328', desc='RP2350B + 2MB flash in package; cart bus server', key='U_RP')
# drawn in two units: A = the 48 GPIOs on the cart-bus sheet, B = supplies, core regulator,
# crystal, RUN, SWD, USB and QSPI on rp-core (gen_sch.rp_split_symbol)
U_RP.unit_sheets = {1: 'cart-bus', 2: 'rp-core'}
U_RP.pin_unit = {str(pad): 1 if pad in RP_GPIO_PIN.values() else 2 for pad in rp}
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R('330R', 'TPA', 'RP_TPA', desc='TPA series', key='R_TPA')
R('330R', 'MRD_N', 'RP_MRD', desc='/MRD series', key='R_MRD')

# -- the data path: the RP puts each byte on GPIO16-23; the 74HCT541 drives D0-D7 while /OE1 (/MRD)
# and /OE2 (/DRIVE | /PWROK) are both low (s2_glue_drive).  5 V CMOS levels: the 1802's VIH is
# 3.5 V at 5 V.  /MRD reaches /OE1 with no gate, so the end of a read releases the bus at once.
# Channels taken in reverse (A8 / Y8 = bit 0, as on FujiNet-5200 Rev0): the edge runs D0..D7 west to
# east seen from the parts side, and the '541 at rotation 270 over those fingers then meets them
# and the RP's GPIO16-23 corner with no crossing (a flow-through buffer cannot reverse a bus).
buf = {1: 'MRD_N', 19: 'OE2_N', 10: 'GND', 20: '+5V'}
buf.update({9 - i: 'RP_D%d' % i for i in range(8)})              # A8..A1 (pins 9..2) = bit 0..7
buf.update({11 + i: 'D%d' % i for i in range(8)})               # Y8..Y1 (pins 11..18) = D0..D7
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R('10k', '+5V', 'CLAIM_N', desc='/CLAIM pull-up: CART CS low while the RP is unpowered or booting',
  key='R_PUCLAIM')
# -- PWR_OK: edge 15 (the console 5 V, before the TPS2116 mux) -> 22k / 100k (0.82 x) -> two '14 Schmitt
# stages (TTL thresholds: VT+ 1.2-1.9 V at VCC 4.5 V, TI SCLS225G 6.5) -> GPIO26; the first stage's
# PWR_OK_N gates the '32.  Console off with the cart on USB: PWR_OK 0, PWR_OK_N 1.
GATES('74HCT14', [('VSENSE', 'PWR_OK_N'), ('PWR_OK_N', 'PWR_OK'), ('GND', NC), ('GND', NC),
                  ('GND', NC), ('GND', NC)], desc='PWR_OK from the console 5V sense', key='U_INV')
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C('10uF', '+5V', desc='5V logic domain bulk', key='C_GLUEBULK')
R('22k', 'CONS_5V', 'VSENSE', desc='console 5V sense divider', key='R_VSH')
R('100k', 'VSENSE', 'GND', desc='console 5V sense -> 0.82 x CONS_5V', key='R_VSL')
# -- the console 5 V for the ADC (GPIO40, not 5 V tolerant): 100k / 100k = 0.5 x, 5.5 V reads 2.75 V;
# 100 nF for the ADC's sample capacitor
R('100k', 'CONS_5V', 'VSENSE_ADC', desc='console 5V -> ADC divider (0.5 x)', key='R_ADCH')
R('100k', 'VSENSE_ADC', 'GND', desc='console 5V -> ADC divider', key='R_ADCL')
C('100nF', 'VSENSE_ADC', desc='ADC sample reservoir', key='C_ADCF')
# -- activity LED straight off GPIO27 (3.3 V): red, ~1.3 mA
R('1k', 'RP_LED', 'RP_LED_A', desc='activity LED series', key='R_LED')
add('D', 'Device:LED', 'red', FP('LED_0603_1608Metric'), {1: 'GND', 2: 'RP_LED_A'},
    mpn='KT-0603R', lcsc='C2286', desc='activity LED (GPIO27)', key='D_LED')
# -- debug UART (GPIO44 TX, GPIO45 RX; 3.3 V only), DNP: fit for bring-up
add('J', 'Connector_Generic:Conn_01x03', 'DBG UART', FP('PinHeader_1x03_P2.54mm_Vertical'),
    {1: 'DBG_TX', 2: 'DBG_RX', 3: 'GND'}, mpn='PZ254V-11-03P', lcsc='C2937625',
    desc='RP debug UART, 3.3 V: 1 TX (GPIO44), 2 RX (GPIO45), 3 GND; fit for bring-up', dnp=True, key='J_DBG')
# -- bring-up pads: the read strobe and TPA, the two glue outputs and their controls, PWR_OK
TP('MRD_N', '/MRD', desc='scope pad: console /MRD (edge 21)', key='TP_MRD')
TP('TPA', 'TPA', desc='scope pad: console TPA, gated by /MRD (edge 19)', key='TP_TPA')
TP('CART_CS', 'CART_CS', desc='scope pad: CART CS (edge 22)', key='TP_CARTCS')
TP('DRIVE_N', '/DRIVE', desc='scope pad: /DRIVE (GPIO24)', key='TP_DRIVE')
TP('CLAIM_N', '/CLAIM', desc='scope pad: NOR input (GPIO25)', key='TP_CLAIM')
TP('PWR_OK', 'PWR_OK', desc='scope pad: console power sense', key='TP_PWROK')
TP('GND', 'GND', desc='scope ground by the bus pads', key='TP_GNDBUS')

# =========================================================================
sheet('rp-core')
# 0402 where a pin's neighbours leave no room for an 0603 straight out of it (IOVDD 50 / DVDD 51, between
# the debug UART and GPIO40: Raspberry Pi's 0402 land, the corner's own 100 nF part)
NARROW = (50, 51)
for pin in RP_IOVDD_PINS:      # one 100 nF per IOVDD pin; the key names the pin it sits on
    C('100nF/0402' if pin in NARROW else '100nF', RP_IO_RAIL, desc='IOVDD decoupling', key='C_IOV%d' % pin)
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C('10uF', RP_IO_RAIL, desc='RP IO rail bulk (LDO output)', key='C_IOBULK')
C('4.7uF/0402w', RP_CORE_RAIL, desc='VREG_VIN input (C_IN, at the pins)', key='C_VREGIN')
for pin in RP_DVDD_PINS:
    C('100nF/0402' if pin in NARROW else '100nF', 'DVDD', desc='DVDD decoupling', key='C_DV%d' % pin)
C('4.7uF/0402w', 'DVDD', desc='core regulator output (C_OUT)', key='C_DVBULK')
R4('33R', RP_CORE_RAIL, 'VREG_AVDD', desc='VREG_AVDD filter', key='R_AVDD')
C('4.7uF/0402', 'VREG_AVDD', desc='VREG_AVDD filter', key='C_AVDD')
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C('15pF', 'XIN', desc='crystal load', key='C_XIN')
C('15pF', 'XOUT_Y', desc='crystal load', key='C_XOUT')
R('1k', 'XOUT', 'XOUT_Y', desc='crystal drive limit', key='R_XOUT')
# RUN / BOOTSEL: the buttons, and the S3 (fnPicoUpdater::forceBootselViaPins(): its pins idle as
# inputs and are driven LOW to assert).  Both chips on 3.3 V rails: a 1k series resistor is the
# whole interface, as on FujiNet-ChannelF Rev0.
R('10k', RP_IO_RAIL, 'RUN', desc='RUN pull-up', key='R_RUN')
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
